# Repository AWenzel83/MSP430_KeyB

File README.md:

# MSP430_KeyB

Custom 60% Keyboard based on a MSP430F5510

Hot Swappable CherryMX Switches, ISO Enter

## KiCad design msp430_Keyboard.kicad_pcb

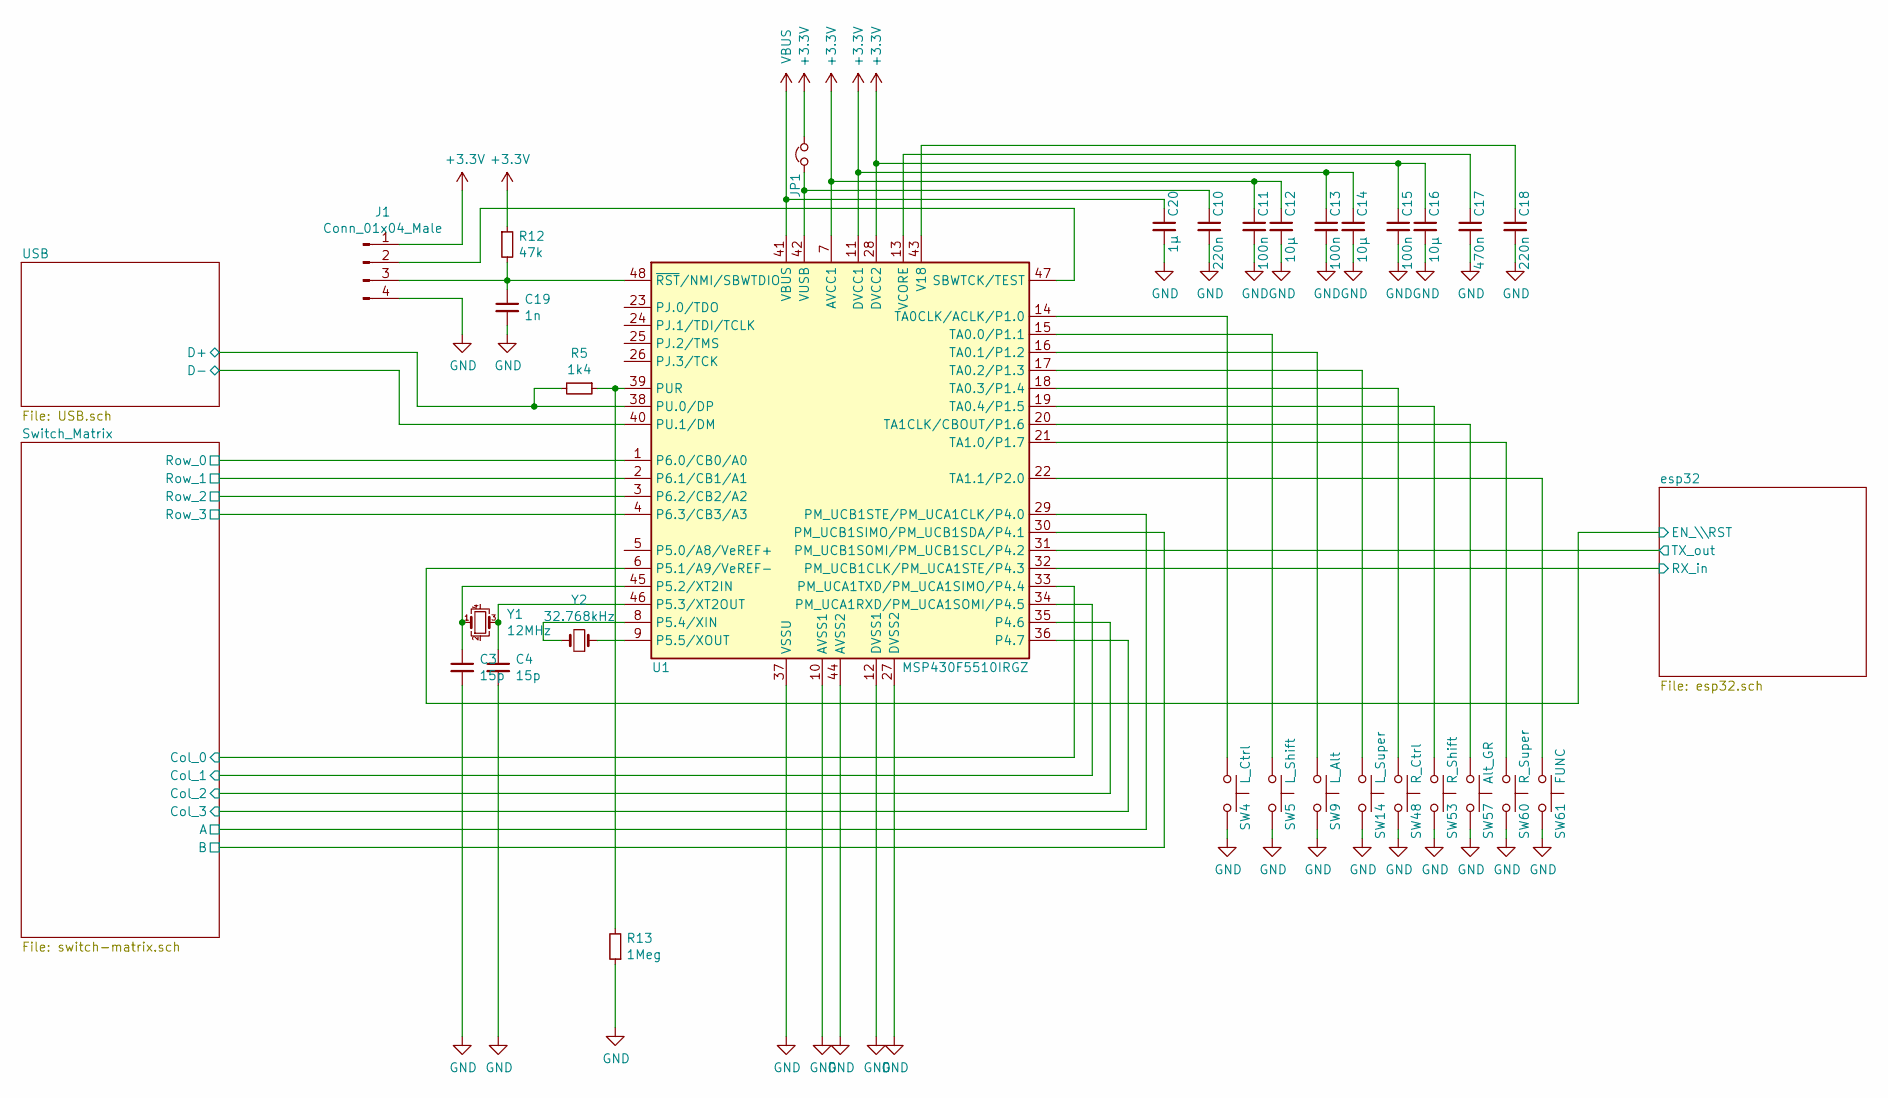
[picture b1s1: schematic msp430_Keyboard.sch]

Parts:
C3, C4: 15p; C_0603_1608Metric_Pad1.08x0.95mm_HandSolder
C10, C18: 220n; C_0603_1608Metric_Pad1.08x0.95mm_HandSolder
C11, C13, C15: 100n; C_0603_1608Metric_Pad1.08x0.95mm_HandSolder
C12, C14, C16: 10µ; C_1206_3216Metric_Pad1.33x1.80mm_HandSolder
C17: 470n; C_0603_1608Metric_Pad1.08x0.95mm_HandSolder
C19: 1n; C_0603_1608Metric_Pad1.08x0.95mm_HandSolder
C20: 1μ; C_0603_1608Metric_Pad1.08x0.95mm_HandSolder
J1: Conn_01x04_Male; PinHeader_1x04_P1.27mm_Horizontal
JP1: Jumper_NC_Small; SolderJumper-2_P1.3mm_Bridged2Bar_RoundedPad1.0x1.5mm
R5: 1k4; R_0603_1608Metric_Pad0.98x0.95mm_HandSolder
R12: 47k; R_0603_1608Metric_Pad0.98x0.95mm_HandSolder
R13: 1Meg; R_0603_1608Metric_Pad0.98x0.95mm_HandSolder
SW4: L_Ctrl; Kailh_MX_Socket
SW5: L_Shift; Kailh_MX_Socket
SW9: L_Alt; Kailh_MX_Socket
SW14: L_Super; Kailh_MX_Socket
SW48: R_Ctrl; Kailh_MX_Socket
SW53: R_Shift; Kailh_MX_Socket
SW57: Alt_GR; Kailh_MX_Socket
SW60: R_Super; Kailh_MX_Socket
SW61: FUNC; Kailh_MX_Socket
U1: MSP430F5510IRGZ; LQFP-48_7x7mm_P0.5mm
Y1: 12MHz; Crystal_SMD_3225-4Pin_3.2x2.5mm
Y2: 32.768kHz; Crystal_SMD_MicroCrystal_MS3V-T1R

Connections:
+3V3: C11.1, C12.1, C13.1, C14.1, C15.1, C16.1, J1.1, JP1.2, R12.1, U1.7 (AVCC1), U1.11 (DVCC1), U1.28 (DVCC2); also elsewhere on the board
/Switch_Matrix/A: U1.29 (PM_UCB1STE/PM_UCA1CLK/P4.0); also elsewhere on the board
/Switch_Matrix/B: U1.30 (PM_UCB1SIMO/PM_UCB1SDA/P4.1); also elsewhere on the board
/Switch_Matrix/Col_0: U1.33 (PM_UCA1TXD/PM_UCA1SIMO/P4.4); also elsewhere on the board
/Switch_Matrix/Col_1: U1.34 (PM_UCA1RXD/PM_UCA1SOMI/P4.5); also elsewhere on the board
/Switch_Matrix/Col_2: U1.35 (P4.6); also elsewhere on the board
/Switch_Matrix/Col_3: U1.36 (P4.7); also elsewhere on the board
/Switch_Matrix/Row_0: U1.1 (P6.0/CB0/A0); also elsewhere on the board
/Switch_Matrix/Row_1: U1.2 (P6.1/CB1/A1); also elsewhere on the board
/Switch_Matrix/Row_2: U1.3 (P6.2/CB2/A2); also elsewhere on the board
/Switch_Matrix/Row_3: U1.4 (P6.3/CB3/A3); also elsewhere on the board
/USB/D+: R5.2, U1.38 (PU.0/DP); also elsewhere on the board
/USB/D-: U1.40 (PU.1/DM); also elsewhere on the board
/esp32/EN_\RST: U1.6 (P5.1/A9/VeREF-); also elsewhere on the board
/esp32/RX_in: U1.32 (PM_UCB1CLK/PM_UCA1STE/P4.3); also elsewhere on the board
/esp32/TX_out: U1.31 (PM_UCB1SOMI/PM_UCB1SCL/P4.2); also elsewhere on the board
GND: C3.2, C4.2, C10.2, C11.2, C12.2, C13.2, C14.2, C15.2, C16.2, C17.2, C18.2, C19.2, C20.2, J1.4, R13.1, SW4.2, SW5.2, SW9.2, SW14.2, SW48.2, SW53.2, SW57.2, SW60.2, SW61.2, U1.10 (AVSS1), U1.12 (DVSS1), U1.27 (DVSS2), U1.37 (VSSU), U1.44 (AVSS2); also elsewhere on the board
unnamed: C3.1, U1.45 (P5.2/XT2IN), Y1.1
unnamed: C4.1, U1.46 (P5.3/XT2OUT), Y1.3
unnamed: C10.1, JP1.1, U1.42 (VUSB)
unnamed: C17.1, U1.13 (VCORE)
unnamed: C18.1, U1.43 (V18)
unnamed: C19.1, J1.3, R12.2, U1.48 (~RST~/NMI/SBWTDIO)
unnamed: J1.2, U1.47 (SBWTCK/TEST)
unnamed: R5.1, R13.2, U1.39 (PUR)
unnamed: SW4.1, U1.14 (TA0CLK/ACLK/P1.0)
unnamed: SW5.1, U1.15 (TA0.0/P1.1)
unnamed: SW9.1, U1.16 (TA0.1/P1.2)
unnamed: SW14.1, U1.17 (TA0.2/P1.3)
unnamed: SW48.1, U1.18 (TA0.3/P1.4)
unnamed: SW53.1, U1.19 (TA0.4/P1.5)
unnamed: SW57.1, U1.20 (TA1CLK/CBOUT/P1.6)
unnamed: SW60.1, U1.21 (TA1.0/P1.7)
unnamed: SW61.1, U1.22 (TA1.1/P2.0)
unnamed: U1.8 (P5.4/XIN), Y2.2
unnamed: U1.9 (P5.5/XOUT), Y2.1
VBUS: C20.1, U1.41 (VBUS); also elsewhere on the board

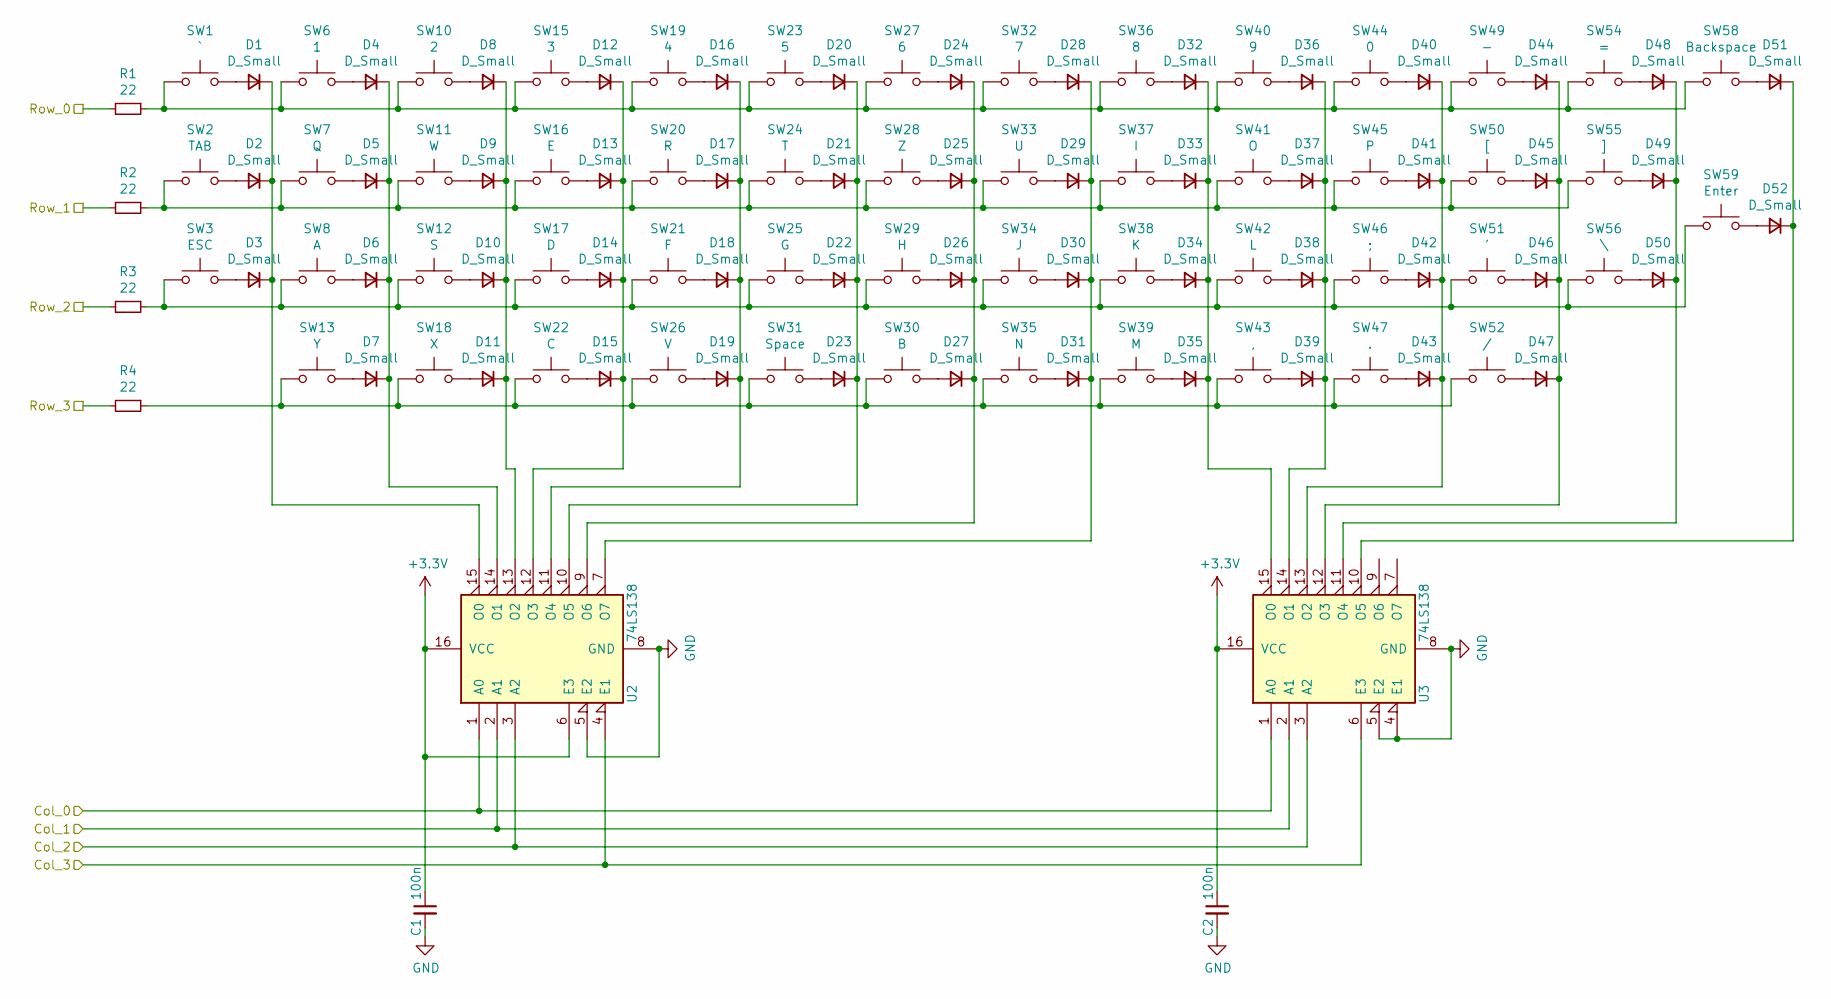
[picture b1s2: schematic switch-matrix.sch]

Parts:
C1, C2: 100n; C_0603_1608Metric
D1, D2, D3, D4, D5, D6, D7, D8, D9, D10, D11, D12, D13, D14, D15, D16, D17, D18, D19, D20, D21, D22, D23, D24, D25, D26, D27, D28, D29, D30, D31, D32, D33, D34, D35, D36, D37, D38, D39, D40, D41, D42, D43, D44, D45, D46, D47, D48, D49, D50, D51, D52: D_Small; D_SOD-323_HandSoldering
R1, R2, R3, R4: 22; R_0603_1608Metric
SW1: `; Kailh_MX_Socket
SW2: TAB; Kailh_MX_Socket
SW3: ESC; Kailh_MX_Socket
SW6: 1; Kailh_MX_Socket
SW7: Q; Kailh_MX_Socket
SW8: A; Kailh_MX_Socket
SW10: 2; Kailh_MX_Socket
SW11: W; Kailh_MX_Socket
SW12: S; Kailh_MX_Socket
SW13: Y; Kailh_MX_Socket
SW15: 3; Kailh_MX_Socket
SW16: E; Kailh_MX_Socket
SW17: D; Kailh_MX_Socket
SW18: X; Kailh_MX_Socket
SW19: 4; Kailh_MX_Socket
SW20: R; Kailh_MX_Socket
SW21: F; Kailh_MX_Socket
SW22: C; Kailh_MX_Socket
SW23: 5; Kailh_MX_Socket
SW24: T; Kailh_MX_Socket
SW25: G; Kailh_MX_Socket
SW26: V; Kailh_MX_Socket
SW27: 6; Kailh_MX_Socket
SW28: Z; Kailh_MX_Socket
SW29: H; Kailh_MX_Socket
SW30: B; Kailh_MX_Socket
SW31: Space; Kailh_MX_Socket
SW32: 7; Kailh_MX_Socket
SW33: U; Kailh_MX_Socket
SW34: J; Kailh_MX_Socket
SW35: N; Kailh_MX_Socket
SW36: 8; Kailh_MX_Socket
SW37: I; Kailh_MX_Socket
SW38: K; Kailh_MX_Socket
SW39: M; Kailh_MX_Socket
SW40: 9; Kailh_MX_Socket
SW41: O; Kailh_MX_Socket
SW42: L; Kailh_MX_Socket
SW43: ,; Kailh_MX_Socket
SW44: 0; Kailh_MX_Socket
SW45: P; Kailh_MX_Socket
SW46: ;; Kailh_MX_Socket
SW47: .; Kailh_MX_Socket
SW49: -; Kailh_MX_Socket
SW50: [; Kailh_MX_Socket
SW51: '; Kailh_MX_Socket
SW52: /; Kailh_MX_Socket
SW54: =; Kailh_MX_Socket
SW55: ]; Kailh_MX_Socket
SW56: \\; Kailh_MX_Socket
SW58: Backspace; Kailh_MX_Socket
SW59: Enter; Kailh_MX_Socket
U2, U3: 74LS138; TSSOP-16_4.4x5mm_P0.65mm

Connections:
+3V3: C1.1, C2.1, U2.6 (E3), U2.16 (VCC), U3.16 (VCC); also elsewhere on the board
/Switch_Matrix/Col_0: U2.1 (A0), U3.1 (A0); also elsewhere on the board
/Switch_Matrix/Col_1: U2.2 (A1), U3.2 (A1); also elsewhere on the board
/Switch_Matrix/Col_2: U2.3 (A2), U3.3 (A2); also elsewhere on the board
/Switch_Matrix/Col_3: U2.4 (E1), U3.6 (E3); also elsewhere on the board
/Switch_Matrix/Row_0: R1.2; also elsewhere on the board
/Switch_Matrix/Row_1: R2.2; also elsewhere on the board
/Switch_Matrix/Row_2: R3.2; also elsewhere on the board
/Switch_Matrix/Row_3: R4.2; also elsewhere on the board
GND: C1.2, C2.2, U2.5 (E2), U2.8 (GND), U3.4 (E1), U3.5 (E2), U3.8 (GND); also elsewhere on the board
unnamed: D1.1 (K), D2.1 (K), D3.1 (K), U2.15 (O0)
unnamed: D1.2 (A), SW1.2
unnamed: D2.2 (A), SW2.1
unnamed: D3.2 (A), SW3.2
unnamed: D4.1 (K), D5.1 (K), D6.1 (K), D7.1 (K), U2.14 (O1)
unnamed: D4.2 (A), SW6.2
unnamed: D5.2 (A), SW7.2
unnamed: D6.2 (A), SW8.2
unnamed: D7.2 (A), SW13.2
unnamed: D8.2 (A), SW10.2
unnamed: D9.2 (A), SW11.2
unnamed: D8.1 (K), D9.1 (K), D10.1 (K), D11.1 (K), U2.13 (O2)
unnamed: D10.2 (A), SW12.2
unnamed: D11.2 (A), SW18.2
unnamed: D12.1 (K), D13.1 (K), D14.1 (K), D15.1 (K), U2.12 (O3)
unnamed: D12.2 (A), SW15.2
unnamed: D13.2 (A), SW16.2
unnamed: D14.2 (A), SW17.2
unnamed: D15.2 (A), SW22.2
unnamed: D16.1 (K), D17.1 (K), D18.1 (K), D19.1 (K), U2.11 (O4)
unnamed: D16.2 (A), SW19.2
unnamed: D17.2 (A), SW20.2
unnamed: D18.2 (A), SW21.2
unnamed: D19.2 (A), SW26.2
unnamed: D20.1 (K), D21.1 (K), D22.1 (K), D23.1 (K), U2.10 (O5)
unnamed: D20.2 (A), SW23.2
unnamed: D21.2 (A), SW24.2
unnamed: D22.2 (A), SW25.1
unnamed: D23.2 (A), SW31.2
unnamed: D24.1 (K), D25.1 (K), D26.1 (K), D27.1 (K), U2.9 (O6)
unnamed: D24.2 (A), SW27.2
unnamed: D25.2 (A), SW28.2
unnamed: D26.2 (A), SW29.2
unnamed: D27.2 (A), SW30.2
unnamed: D28.1 (K), D29.1 (K), D30.1 (K), D31.1 (K), U2.7 (O7)
unnamed: D28.2 (A), SW32.2
unnamed: D29.2 (A), SW33.2
unnamed: D30.2 (A), SW34.2
unnamed: D31.2 (A), SW35.2
unnamed: D32.1 (K), D33.1 (K), D34.1 (K), D35.1 (K), U3.15 (O0)
unnamed: D32.2 (A), SW36.2
unnamed: D33.2 (A), SW37.2
unnamed: D34.2 (A), SW38.2
unnamed: D35.2 (A), SW39.2
unnamed: D36.1 (K), D37.1 (K), D38.1 (K), D39.1 (K), U3.14 (O1)
unnamed: D36.2 (A), SW40.2
unnamed: D37.2 (A), SW41.2
unnamed: D38.2 (A), SW42.2
unnamed: D39.2 (A), SW43.2
unnamed: D40.1 (K), D41.1 (K), D42.1 (K), D43.1 (K), U3.13 (O2)
unnamed: D40.2 (A), SW44.2
unnamed: D41.2 (A), SW45.2
unnamed: D42.2 (A), SW46.2
unnamed: D43.2 (A), SW47.2
unnamed: D44.1 (K), D45.1 (K), D46.1 (K), D47.1 (K), U3.12 (O3)
unnamed: D44.2 (A), SW49.2
unnamed: D45.2 (A), SW50.2
unnamed: D46.2 (A), SW51.2
unnamed: D47.2 (A), SW52.2
unnamed: D48.1 (K), D49.1 (K), D50.1 (K), U3.11 (O4)
unnamed: D48.2 (A), SW54.2
unnamed: D49.2 (A), SW55.2
unnamed: D50.2 (A), SW56.2
unnamed 88: D51.1 (K), D52.1 (K), U3.10 (O5); also elsewhere on the board
unnamed: D51.2 (A), SW58.2
unnamed: D52.2 (A), SW59.2
unnamed: R1.1, SW1.1, SW6.1, SW10.1, SW15.1, SW19.1, SW23.1, SW27.1, SW32.1, SW36.1, SW40.1, SW44.1, SW49.1, SW54.1, SW58.1
unnamed 103: R2.1, SW2.2, SW7.1, SW11.1, SW16.1, SW20.1, SW24.1, SW28.1, SW33.1, SW37.1, SW41.1, SW45.1, SW50.1, SW55.1; also elsewhere on the board
unnamed: R3.1, SW3.1, SW8.1, SW12.1, SW17.1, SW21.1, SW25.2, SW29.1, SW34.1, SW38.1, SW42.1, SW46.1, SW51.1, SW56.1, SW59.1
unnamed: R4.1, SW13.1, SW18.1, SW22.1, SW26.1, SW30.1, SW31.1, SW35.1, SW39.1, SW43.1, SW47.1, SW52.1

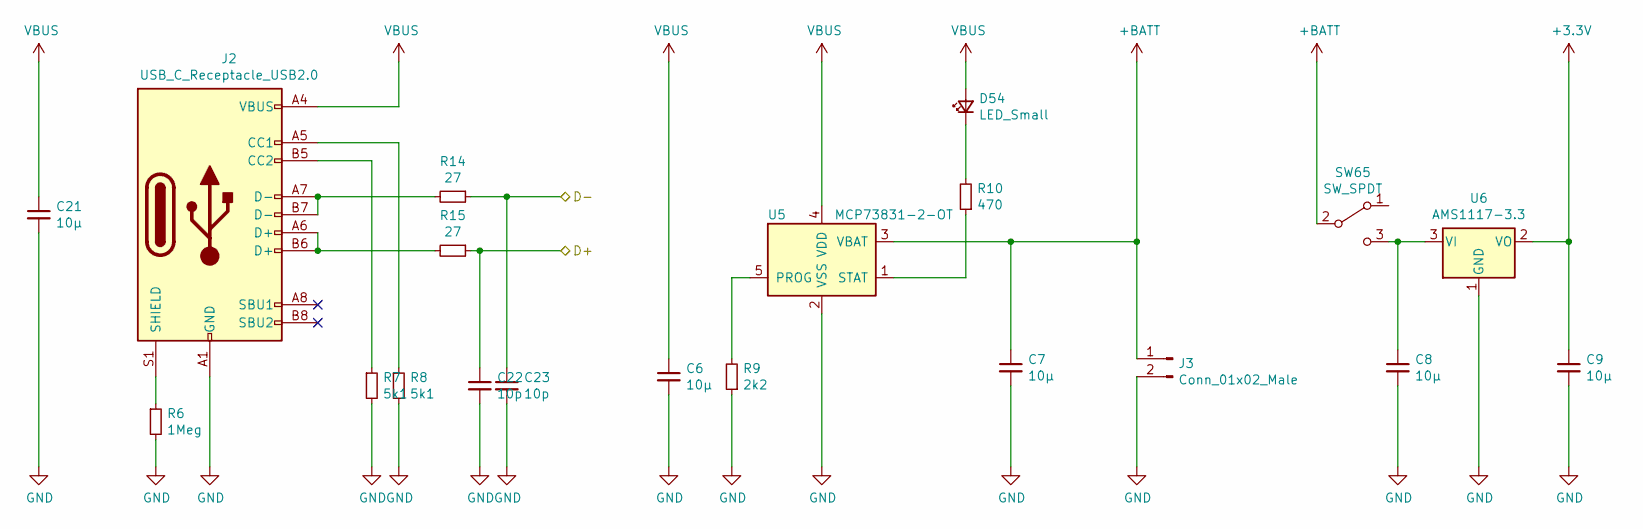
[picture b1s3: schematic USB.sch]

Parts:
C6, C7, C8, C9: 10µ; C_1206_3216Metric_Pad1.33x1.80mm_HandSolder
C21: 10μ; C_1206_3216Metric_Pad1.33x1.80mm_HandSolder
C22, C23: 10p; C_0603_1608Metric_Pad1.08x0.95mm_HandSolder
D54: LED_Small; LED_0603_1608Metric_Pad1.05x0.95mm_HandSolder
J2: USB_C_Receptacle_USB2.0; 632723300011
J3: Conn_01x02_Male; JST_PH_S2B-PH-K_1x02_P2.00mm_Horizontal
R6: 1Meg; R_0603_1608Metric_Pad0.98x0.95mm_HandSolder
R7, R8: 5k1; R_0603_1608Metric_Pad0.98x0.95mm_HandSolder
R9: 2k2; R_0603_1608Metric_Pad0.98x0.95mm_HandSolder
R10: 470; R_0603_1608Metric_Pad0.98x0.95mm_HandSolder
R14, R15: 27; R_0603_1608Metric_Pad0.98x0.95mm_HandSolder
SW65: SW_SPDT; APEM_SLG12014
U5: MCP73831-2-OT; SOT-23-5
U6: AMS1117-3.3; SOT-223-3_TabPin2

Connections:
+3V3: C9.1, U6.2 (VO); also elsewhere on the board
+BATT: C7.1, J3.1, SW65.2 (B), U5.3 (VBAT)
/USB/D+: C22.1, R15.1; also elsewhere on the board
/USB/D-: C23.1, R14.1; also elsewhere on the board
GND: C6.2, C7.2, C8.2, C9.2, C21.2, C22.2, C23.2, J2.A1 (GND), J2.A12 (GND), J2.B1 (GND), J2.B12 (GND), J3.2, R6.2, R7.2, R8.2, R9.1, U5.2 (VSS), U6.1 (GND); also elsewhere on the board
unnamed: C8.1, SW65.3 (C), U6.3 (VI)
unnamed: D54.1 (K), R10.2
unnamed: J2.A5 (CC1), R8.1
unnamed: J2.A6 (D+), J2.B6 (D+), R15.2
unnamed: J2.A7 (D-), J2.B7 (D-), R14.2
unnamed: J2.B5 (CC2), R7.1
unnamed: J2.S1 (SHIELD), R6.1
unnamed: R9.2, U5.5 (PROG)
unnamed: R10.1, U5.1 (STAT)
VBUS: C6.1, C21.1, D54.2 (A), J2.A4 (VBUS), J2.A9 (VBUS), J2.B4 (VBUS), J2.B9 (VBUS), U5.4 (VDD); also elsewhere on the board

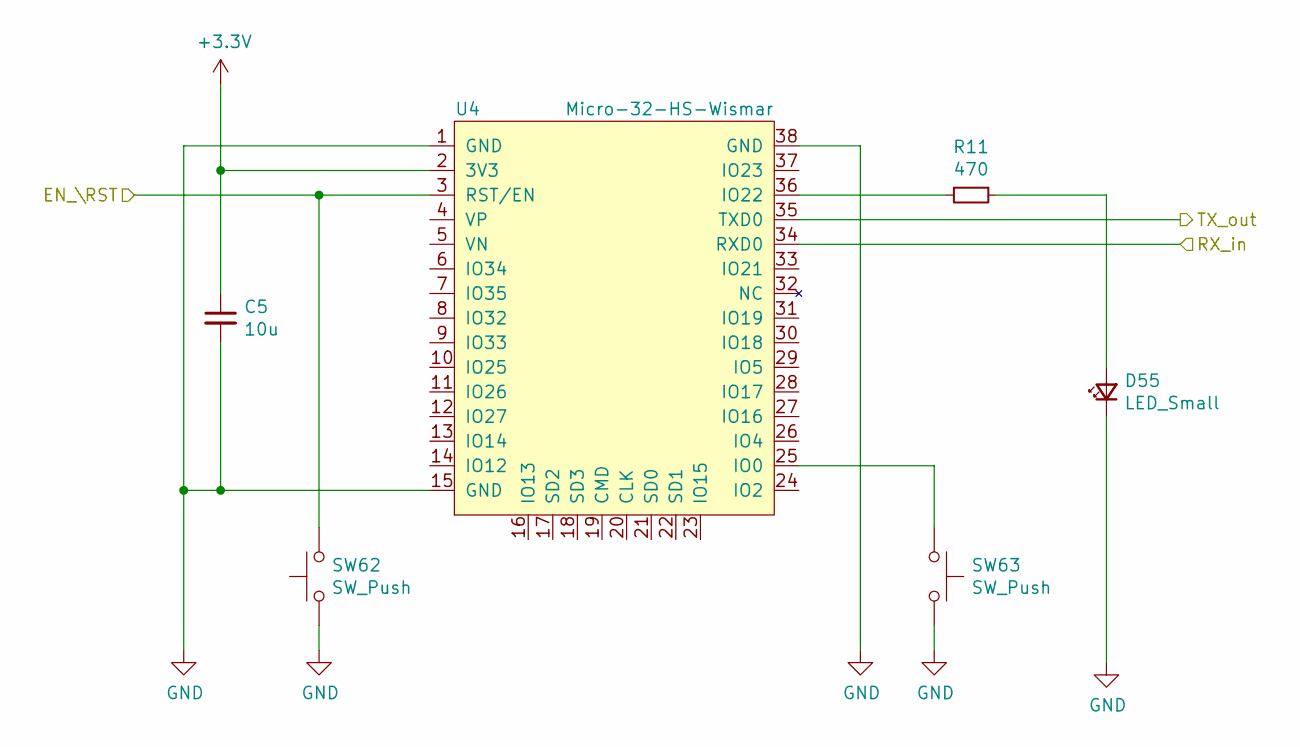
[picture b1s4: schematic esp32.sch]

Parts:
C5: 10u; C_1206_3216Metric_Pad1.33x1.80mm_HandSolder
D55: LED_Small; LED_D3.0mm_Horizontal_O1.27mm_Z2.0mm
R11: 470; R_0603_1608Metric_Pad0.98x0.95mm_HandSolder
SW62, SW63: SW_Push; SW_Push_1P1T_NO_CK_KMR2
U4: Micro-32-HS-Wismar; micro32

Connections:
+3V3: C5.1, U4.2 (3V3); also elsewhere on the board
/esp32/EN_\RST: SW62.2, U4.3 (RST/EN); also elsewhere on the board
/esp32/RX_in: U4.34 (RXD0); also elsewhere on the board
/esp32/TX_out: U4.35 (TXD0); also elsewhere on the board
GND: C5.2, D55.1 (K), SW62.1, SW63.2, U4.1 (GND), U4.15 (GND), U4.38 (GND); also elsewhere on the board
unnamed: D55.2 (A), R11.1
unnamed: R11.2, U4.36 (IO22)
unnamed: SW63.1, U4.25 (IO0)

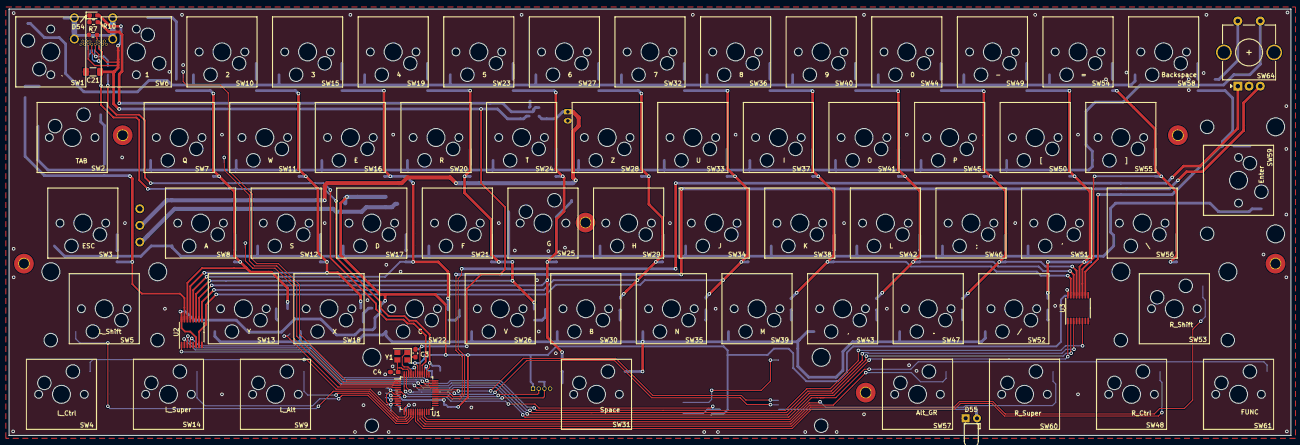
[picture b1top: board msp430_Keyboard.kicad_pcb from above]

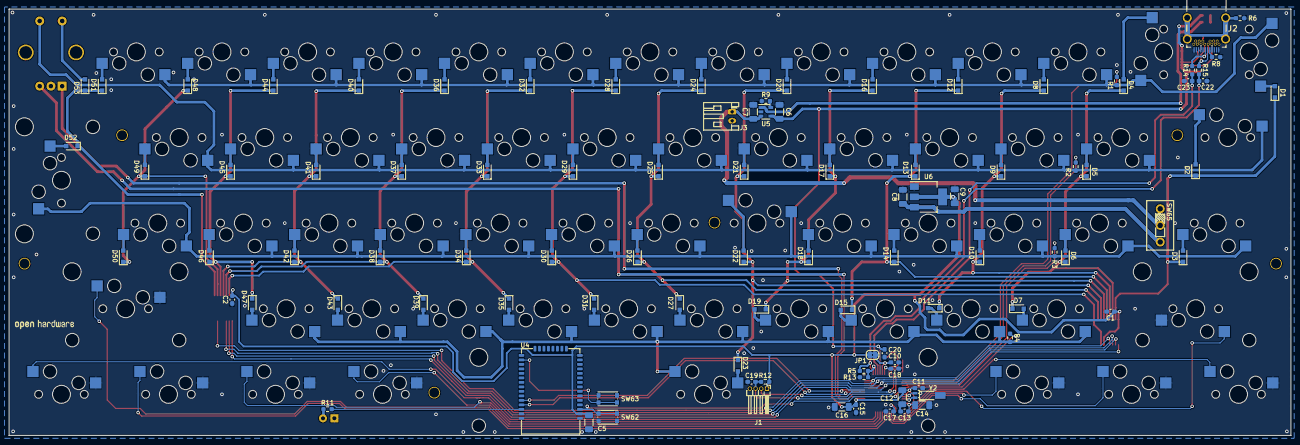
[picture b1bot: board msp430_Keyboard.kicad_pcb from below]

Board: 2 copper layers, 285.2 x 94.9 mm, 170 parts (97 on the bottom side), 121 nets.

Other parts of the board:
D53: D_Small; D_SOD-323_HandSoldering
SW64: Rotary_Encoder_Switch; RotaryEncoder_Alps_EC11E-Switch_Vertical_H20mm_CircularMoun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

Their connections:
/Switch_Matrix/A: SW64.A; also elsewhere on the board
/Switch_Matrix/B: SW64.B; also elsewhere on the board
GND: SW64.C; also elsewhere on the board
unnamed 88: D53.1; also elsewhere on the board
unnamed: D53.2, SW64.S2
unnamed 103: SW64.S1; also elsewhere on the board

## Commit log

2021-06-13 License added
2021-06-13 USB-Connector und Vogelfutter
2021-06-14 USB-Part und ESP32
2021-06-14 Rotated Keys to make room for USB-C-Port
2021-06-17 Rotary Encoder added
2021-07-23 Routing angefangen
2021-07-25 Layout fortgesetzt
2021-07-28 Layout sent to JLCPCB
2021-08-19 Filterung in den USB-Leitungen, VBus besser abgeblockt, Enter Taste gedreht
